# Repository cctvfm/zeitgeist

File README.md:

# zeitgeist
Zeitgeist is a design for a delay effect/sound source based around heavy abuse of a PT2399 karaoke delay chip devised by Rob Hordijk.

Eagle .sch and .brd provided, along with gerbers ready to go.
BOM included
Art Included
Tayda Enclosure Drill Template:
https://drill.taydakits.com/box-designs/new?public_key=bjFJdjJ0OW5hZGFLbC9yd1lEM01qQT09Cg==

This fits in a 1590BB2 enclosure. The jack and switch PCBs aren't strictly necessary if you don't mind doing some more wiring.

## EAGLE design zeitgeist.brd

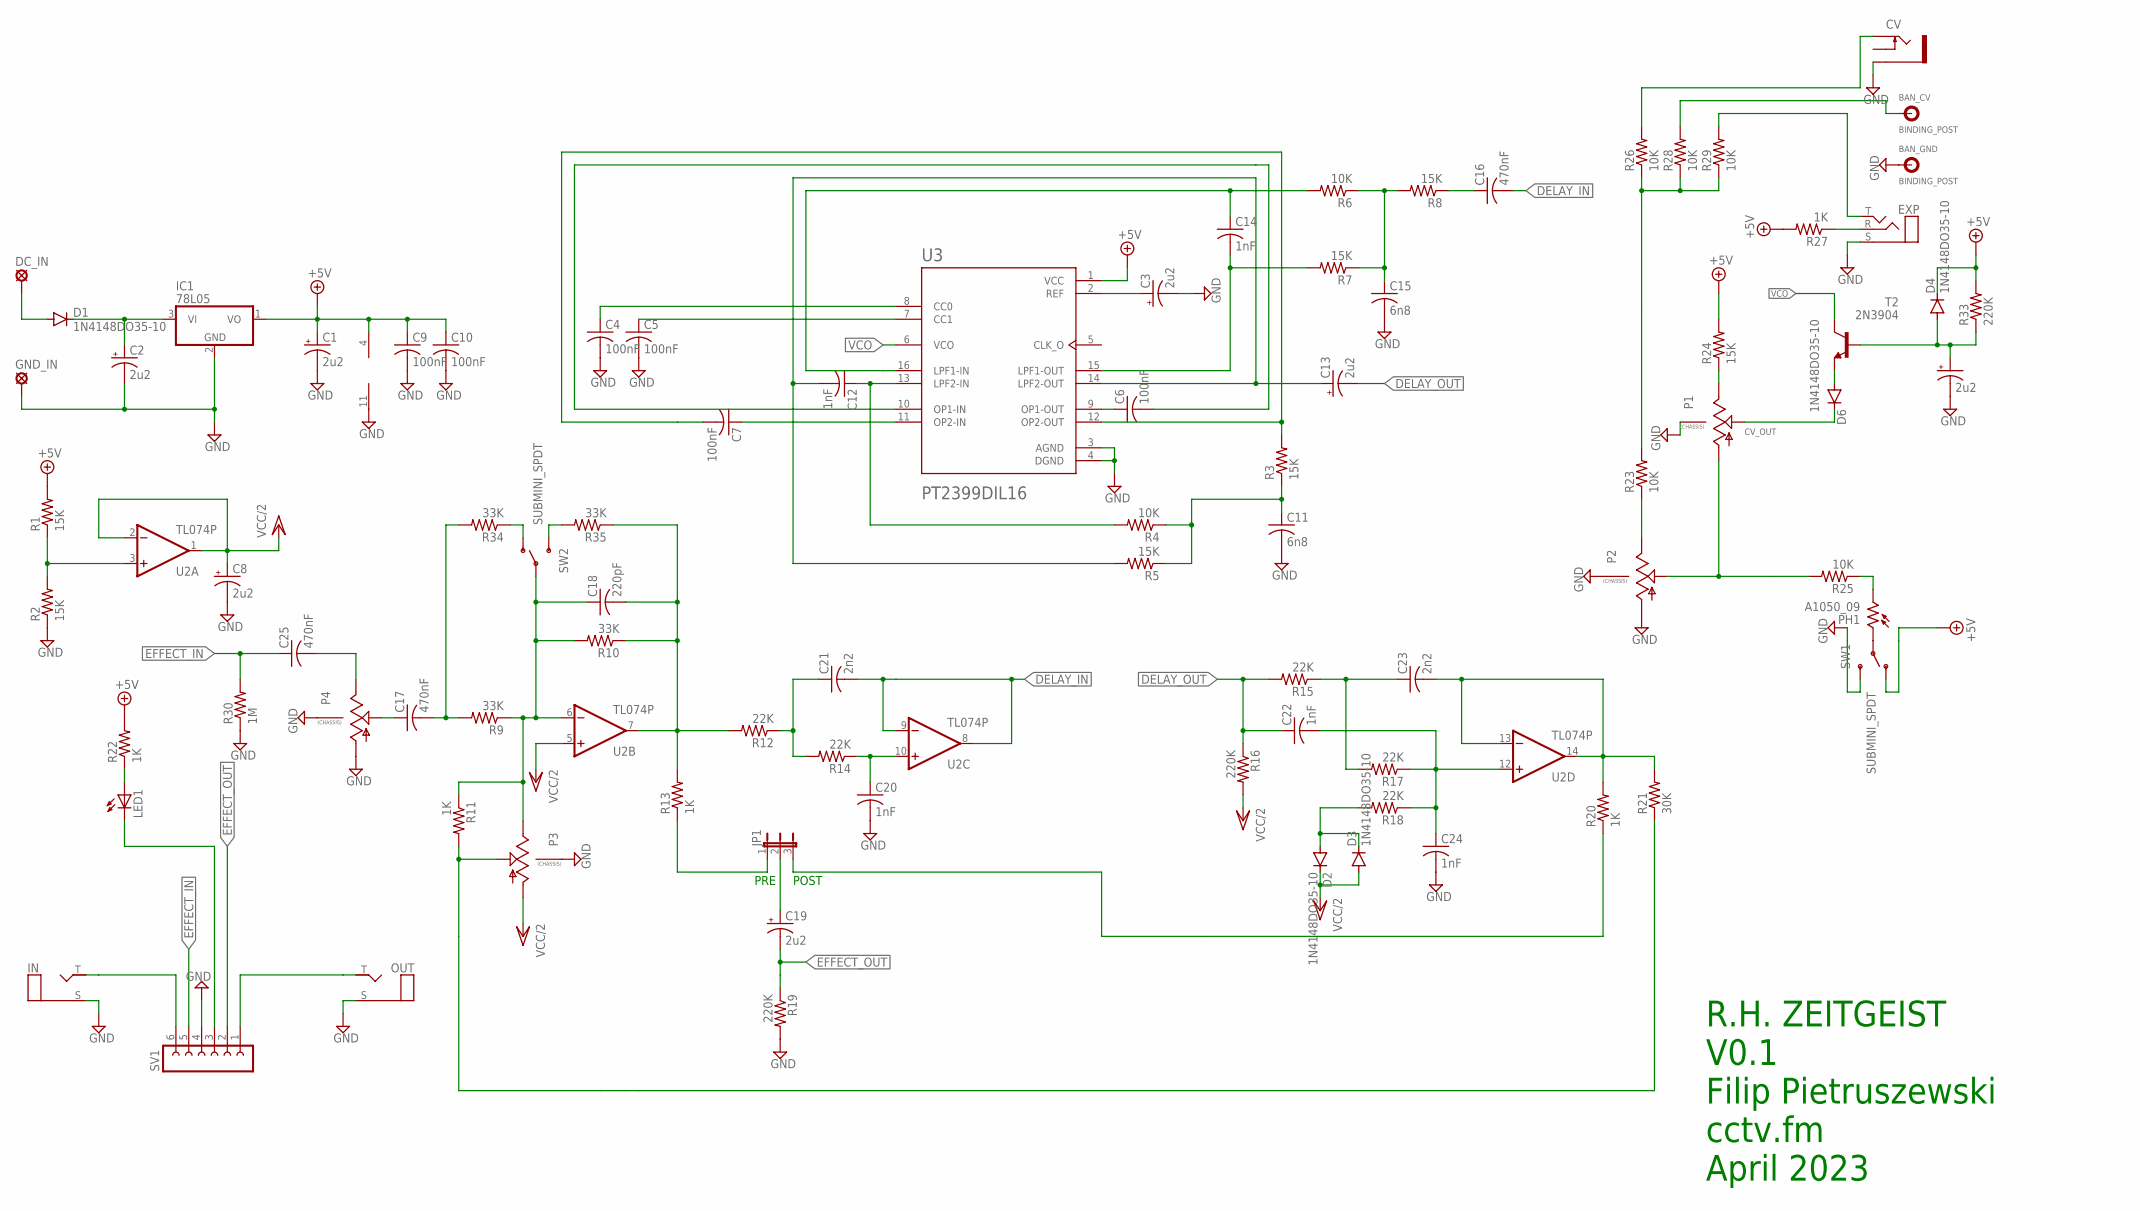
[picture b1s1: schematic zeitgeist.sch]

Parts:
BAN_CV: BINDING_POST
BAN_GND: BINDING_POST
C1, C2, C3, C8, C13, C19, C26: 2u2; E2,5-6
C4, C5, C9, C10: 100nF; C050-024X044
C6, C7: 100nF; C050-035X075
C11, C15: 6n8; C050-035X075
C12, C14, C20, C22, C24: 1nF; C050-035X075
C16, C17, C25: 470nF; C050-035X075
C18: 220pF; C050-035X075
C21, C23: 2n2; C050-035X075
CV: THONKICONNNEW; WQP-PJ301M-12_JACK
D1, D2, D3, D4, D6: 1N4148DO35-10; DO35-10
DC_IN: SE14
EXP: STEREO_PADS; 3PADS
GND_IN: SE14
IC1: 78L05; TO92
IN: MONO_PADS; 2PADS
JP1: JP2E; JP2
LED1: LED5MM
OUT: MONO_PADS; 2PADS
P1, P2, P3, P4: 9MM_SNAP-IN_POT_CHASSIS; 9MM_SNAP-IN_POT
PH1: A1050_09; T0-46-A10XX
R1, R2, R3, R5, R7, R8, R24: 15K; 0204/7
R4, R6, R23, R25, R26, R28, R29: 10K; 0204/7
R9, R10, R34, R35: 33K; 0204/7
R11, R13, R20, R22, R27: 1K; 0204/7
R12, R14, R15, R17, R18: 22K; 0204/7
R16, R19, R33: 220K; 0204/7
R21: 30K; 0204/7
R30: 1M; 0204/7
SV1: FE06-1; FE06
SW1, SW2: SUBMINI_SPDT; SUBMINI_TOGGLE
T2: 2N3904; TO92
U2: TL074P; DIL14
U3: PT2399DIL16; DIL16

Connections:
+5V: C1.+, C9.1, C10.1, D4.C, IC1.1 (VO), R1.2, R22.2, R24.2, R27.2, R33.2, SW1.1 (O), U2.4 (V+), U3.1 (VCC)
CV_IN: CV.P$1_TIP (TIP), R26.2
CV_OUT: D6.C, P1.2 (S)
DELAY_IN: C16.2, C21.2, U2.8 (OUT), U2.9 (-IN)
DELAY_OUT: C13.-, C22.1, R15.2, R16.1
EFFECT_IN: C25.1, R30.2, SV1.5
EFFECT_OUT: C19.-, R19.1, SV1.2
GND: BAN_GND.P$1, C1.-, C2.-, C3.-, C4.2, C5.2, C8.-, C9.2, C10.2, C11.2, C15.2, C20.2, C24.2, C26.-, CV.P$3_SLEEVE (SLEEVE), EXP.S, GND_IN.MP, IC1.2 (GND), IN.S, OUT.S, P1.CHASSIS1, P1.CHASSIS2, P2.1 (A), P2.CHASSIS1, P2.CHASSIS2, P3.CHASSIS1, P3.CHASSIS2, P4.1 (A), P4.CHASSIS1, P4.CHASSIS2, R2.1, R19.2, R30.1, SV1.4, SW1.3 (S), U2.11 (V-), U3.3 (AGND), U3.4 (DGND)
unnamed: C2.+, D1.C, IC1.3 (VI)
unnamed: C6.2, U3.10 (OP1-IN)
unnamed: C6.1, U3.9 (OP1-OUT)
unnamed: C7.1, U3.11 (OP2-IN)
unnamed: C3.+, U3.2 (REF)
unnamed: C7.2, R3.2, U3.12 (OP2-OUT)
unnamed: R1.1, R2.2, U2.3 (+IN)
unnamed: C5.1, U3.7 (CC1)
unnamed: C4.1, U3.8 (CC0)
unnamed: C11.1, R3.1, R4.1, R5.1
unnamed: C12.1, R4.2, U3.13 (LPF2-IN)
unnamed: C23.1, R15.1, R17.2
unnamed: C12.2, C13.+, R5.2, U3.14 (LPF2-OUT)
unnamed: C14.1, R6.2, U3.16 (LPF1-IN)
unnamed: C14.2, R7.2, U3.15 (LPF1-OUT)
unnamed: C15.1, R6.1, R7.1, R8.2
unnamed: C16.1, R8.1
unnamed: D1.A, DC_IN.MP
unnamed: C17.1, P4.2 (S)
unnamed: C18.1, P3.3 (E), R9.1, R10.2, R11.1, SW2.COM (COMMON), U2.6 (-IN)
unnamed: C17.2, R9.2, R34.2
unnamed: P3.2 (S), R11.2, R21.1
unnamed: C18.2, R10.1, R12.2, R13.2, R35.1, U2.7 (OUT)
unnamed: C19.+, JP1.2
unnamed: JP1.1, R13.1
unnamed: C21.1, R12.1, R14.2
unnamed: C20.1, R14.1, U2.10 (+IN)
unnamed: C22.2, C24.1, R17.1, R18.1, U2.12 (+IN)
unnamed: D2.A, D3.C, R18.2
unnamed: LED1.A, R22.1
unnamed: C23.2, R20.2, R21.2, U2.13 (-IN), U2.14 (OUT)
unnamed: P2.3 (E), R23.1
unnamed: JP1.3, R20.1
unnamed: P1.1 (A), P2.2 (S), R25.2
unnamed: P1.3 (E), R24.1
unnamed: D6.A, T2.3 (E)
unnamed: PH1.2, R25.1
unnamed: PH1.1, SW1.COM (COMMON)
unnamed: R23.2, R26.1, R28.1, R29.1
unnamed: EXP.R, R27.1
unnamed: LED1.K (C), SV1.3
unnamed: C25.2, P4.3 (E)
unnamed: IN.T, SV1.6
unnamed: EXP.T, R29.2
unnamed: BAN_CV.P$1, R28.2
unnamed: OUT.T, SV1.1
unnamed: R35.2, SW2.3 (S)
unnamed: R34.1, SW2.1 (O)
unnamed: C26.+, D4.A, R33.1, T2.2 (B)
VCC/2: C8.+, D2.C, D3.A, P3.1 (A), R16.2, U2.1 (OUT), U2.2 (-IN), U2.5 (+IN)
VCO: T2.1 (C), U3.6 (VCO)

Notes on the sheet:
R.H. ZEITGEIST V0.1 Filip Pietruszewski cctv.fm April 2023
PRE
POST

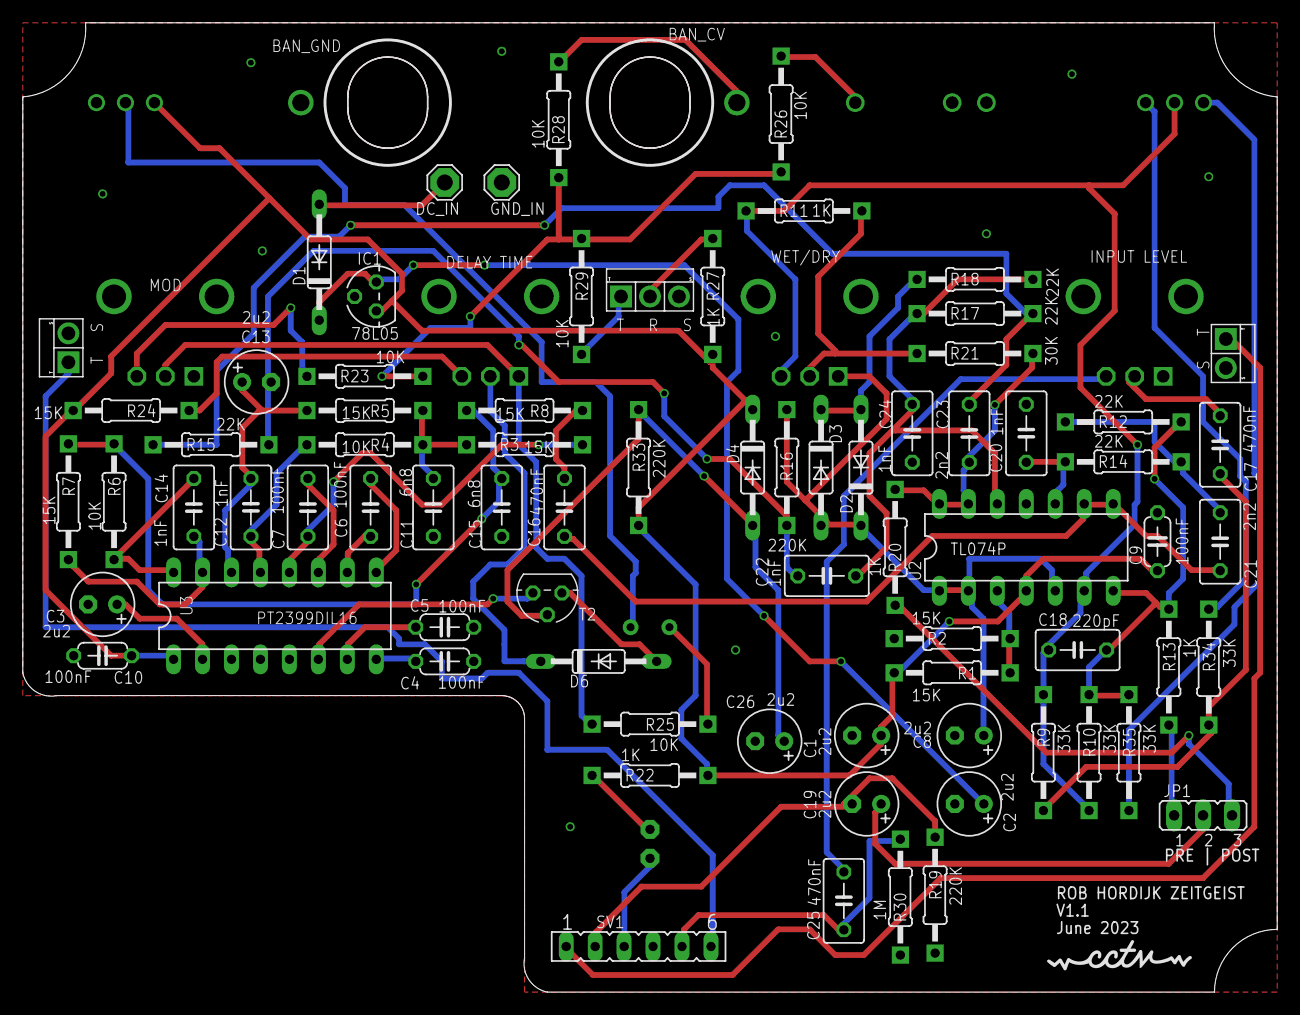
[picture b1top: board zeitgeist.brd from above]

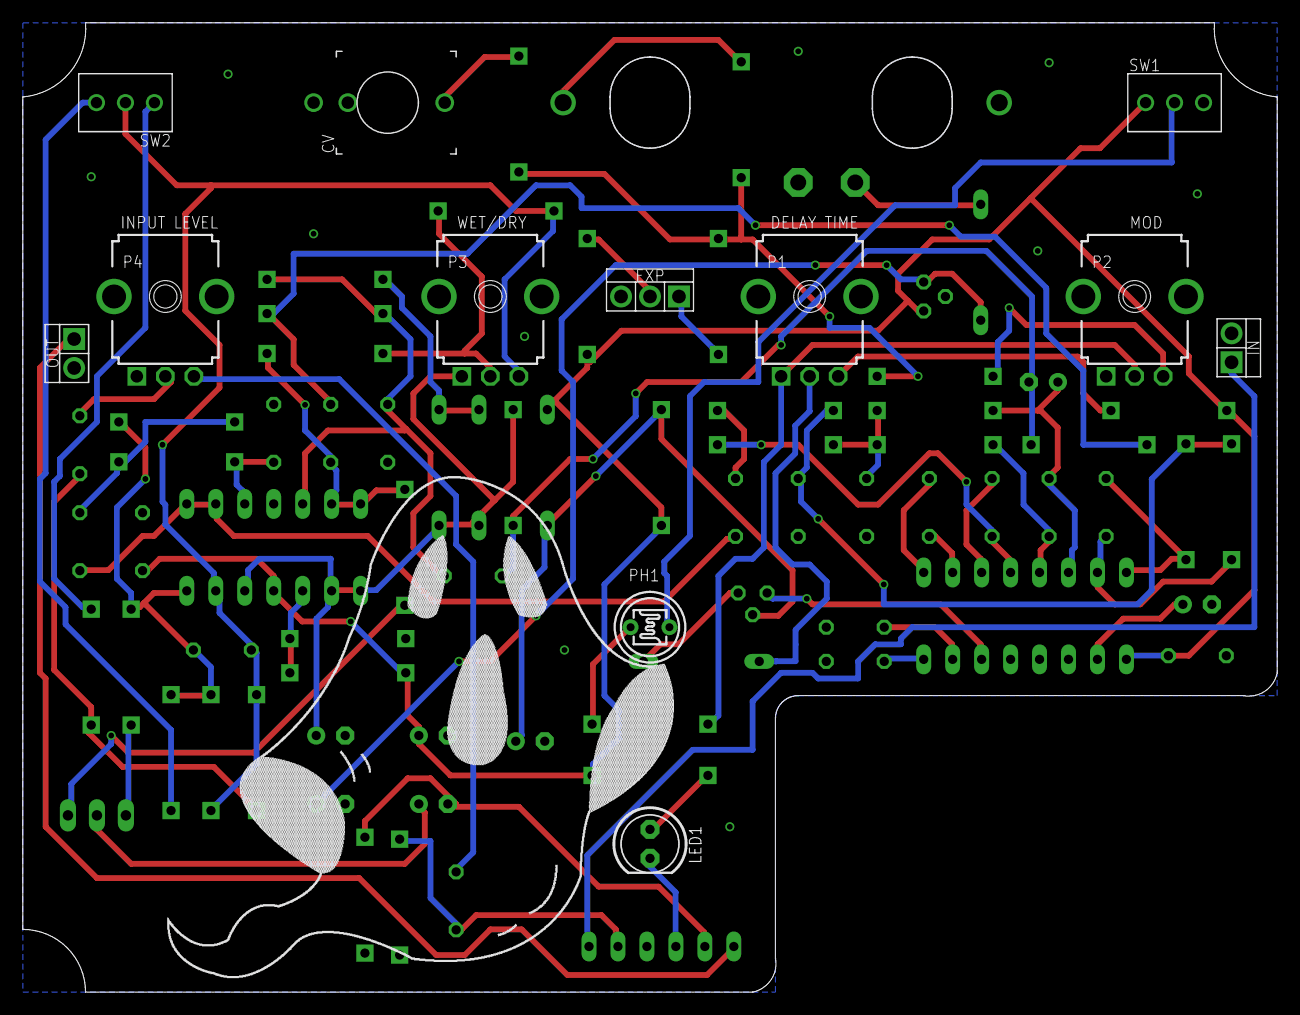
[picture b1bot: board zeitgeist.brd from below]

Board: 2 copper layers, 109.9 x 84.9 mm, 86 parts (9 on the bottom side), 59 nets.

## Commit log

2023-05-26 Added Initial files
2023-05-26 Add files via upload
    Added 3pdt pcb and jackpack pcb
2023-05-26 Add files via upload
    Uploaded Schematic PDF
2023-06-08 Fixed reversed Time and Mod pots

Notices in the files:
parts and their libraries:
SparkFun-Connectors: Licensing: Creative Commons ShareAlike 4.0 International - https://creativecommons.org/licenses/by-sa/4.0
